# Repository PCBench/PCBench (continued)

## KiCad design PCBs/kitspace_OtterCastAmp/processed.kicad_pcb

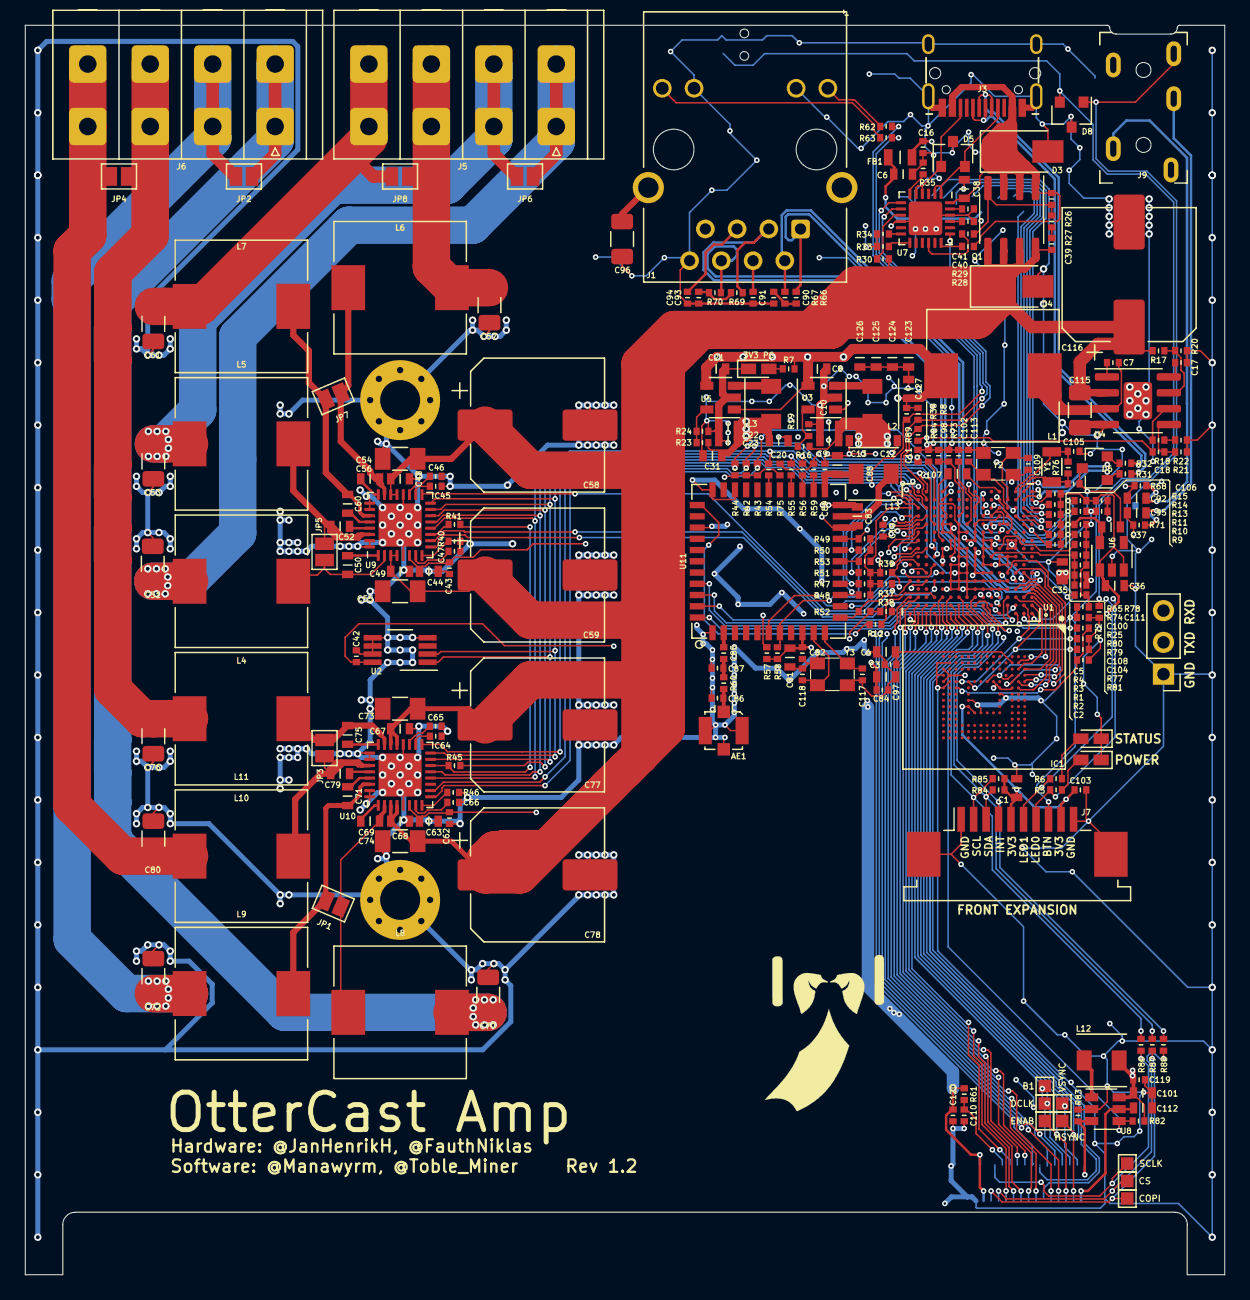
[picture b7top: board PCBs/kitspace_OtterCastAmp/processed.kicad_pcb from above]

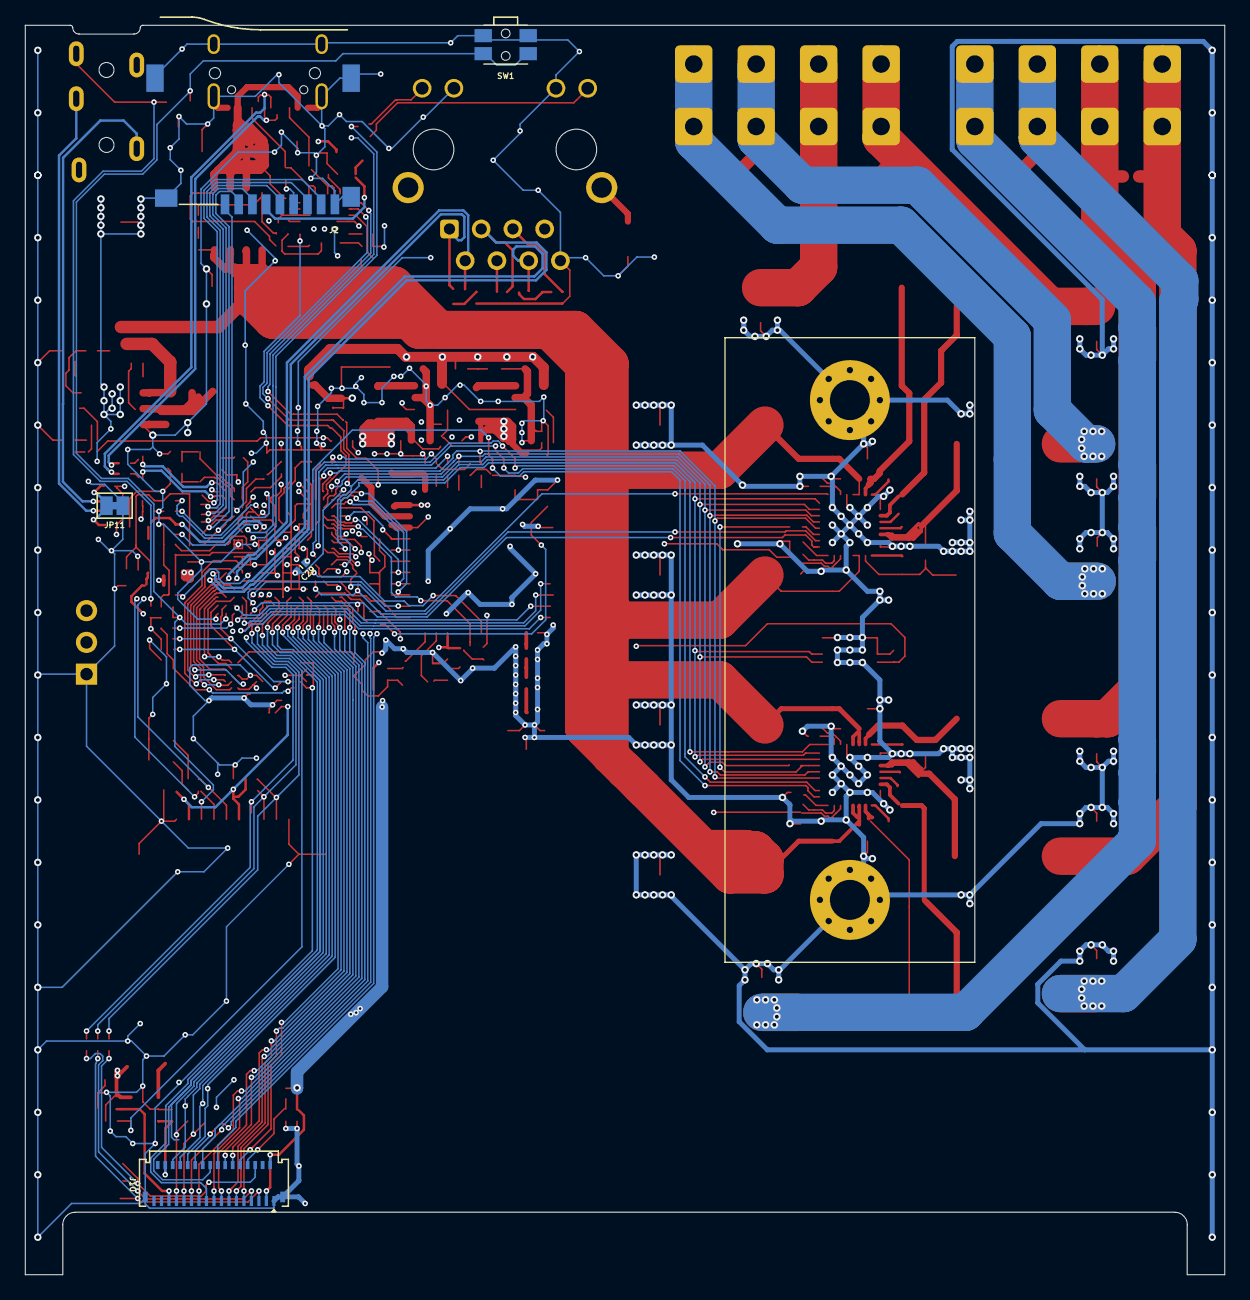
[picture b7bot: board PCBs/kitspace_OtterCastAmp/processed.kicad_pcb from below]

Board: 4 copper layers, 96.0 x 100.0 mm, 269 parts (5 on the bottom side), 203 nets.

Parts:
3V3 PG: LED; LED_0603_1608Metric
AE1: u.FL; U.FL_Molex_MCRF_73412-0110_Vertical
B1: TestPoint; TestPoint_Pad_1.0x1.0mm
C1, C4, C6, C8, C9, C10, C12, C13, C20, C21, C22, C23, C31, C35, C36, C37, C44, C63, C81, C83, C88, C97, C101, C107, C123, C124, C125, C126, C127: 10u; C_0603
C2, C86, C87: DNP; C_0402
C3, C5, C11, C16, C17, C19, C29, C39, C42, C43, C62, C82, C84, C89, C90, C91, C93, C94, C98, C100, C102, C103, C104, C108, C110, C111, C119, C120: 100n; C_0402
C7: 10n; C_0402
C18: 3.3n; C_0402
C38, C92, C95: 1u 25V; C_0603
C40, C41, C45, C46, C47, C64, C65, C66: 1u; C_0402
C48, C49, C67, C68: 100n 50V; C_0603
C50, C52, C56, C60, C69, C71, C75, C79, C112: 470n 25V; C_0603
C51, C53, C57, C61, C70, C72, C76, C80: 680n 50V; C_1206_3216Metric
C54, C55, C73, C74, C115: 22u 50V; C_1206_3216Metric
C58, C59, C77, C78, C116: 470u 35V; CP_Elec_10x10.5
C85, C105, C106, C109, C113: 18p; C_0402
C96: 1n 2kV; C_1206_3216Metric
C117, C118: 22pF; C_0402
COPI: TestPoint; TestPoint_Pad_1.0x1.0mm
CS: TestPoint; TestPoint_Pad_1.0x1.0mm
D1, D2: LED; LED_0603_1608Metric
D3, D4: SMAJ22A; D_SMA
D5, D6, D8: ESD5302F; SOT-23
DCLK: TestPoint; TestPoint_Pad_1.0x1.0mm
ENAB: TestPoint; TestPoint_Pad_1.0x1.0mm
FB1: FERRET; R_0805
H1, H2: 3.2mm; MountingHole_3.2mm_M3_Pad_Via
HSYNC: TestPoint; TestPoint_Pad_1.0x1.0mm
IC1: EMMC04G-S100-B08U; MICRON_EMMC_153
J1: HR911105A; RJ45_Hanrun_HR911105A
J2: Micro_SD_Card; SUNTECH_ST-TF-003A
J3: USB; USB-C 16Pin
J4: UART1; PinHeader_1x03_P2.54mm_Vertical
J5, J6: C475204
J7: AFA07-S10FCC-00; TE_1-84952-0_1x10-1MP_P1.0mm_Horizontal
J9: PJ-3270
J10: FH26W-33S-0.3SHW; Molex_502250-3391_2Rows-33Pins-1MP_P0.60mm_Horizontal
JP1, JP2, JP3, JP4, JP5, JP6, JP7, JP8: PBTL; SolderJumper-2_P1.3mm_Open_Pad1.0x1.5mm
JP11: GNDA; SolderJumper-2_P1.3mm_Bridged_Pad1.0x1.5mm
L1: 15uH; L_10.4x10.4_H4.8
L2, L3: 2u2; Inductor_4040
L4, L5, L6, L7, L8, L9, L10, L11: 10u; L_10.4x10.4_H4.8
L12: 22u; Inductor_4040
L13: 2.2uH; Inductor_4040
Q1: DMP4015SS; SOIC-8_3.9x4.9mm_P1.27mm
R1, R2, R4, R9, R10, R11, R13, R14, R15, R18, R20, R47, R48, R49, R50, R51, R52, R57, R58, R61: 47k; R_0402
R3, R12, R25, R53, R59, R64: 22; R_0402
R5, R6, R7, R8, R28, R36, R62, R63, R77, R79, R84, R85, R89: 2.2k; R_0402
R16, R17, R23, R24, R26, R33, R34, R35, R78: 100k; R_0402
R19: 68k; R_0402
R21: 15k; R_0402
R22, R75: 5.6k; R_0402
R27, R54, R55, R56: 100R; R_0402
R29: 22k; R_0402
R30, R46: 1k; R_0402
R31, R32, R40, R41, R60, R86, R87, R88: 0R; R_0402
R37, R38, R39, R42, R43, R44, R65, R82: 10k; R_0402
R45, R68, R71: DNP; R_0402
R66, R67, R69, R70: 51; R_0402
R72, R73: 200k; R_0402
R74: 6k04; R_0402
R76: 10M; R_0402
R80, R81: 240; R_0402
R83: 10R; R_0402
SCLK: TestPoint; TestPoint_Pad_1.0x1.0mm
SW1: CONFIG; SW_SPST_EVQP7C
U1: AllWinner-S3(FBGA-234); FBGA-234(Pitch-0.65mm_Pad-0.3mm_11x11x1.08mm)
U2: LM75B; VSSOP-8_3.0x3.0mm_P0.65mm
U3, U5: SY8089AAAC; SOT-23-5
U4: MP2303; SOIC-8-1EP_3.9x4.9mm_P1.27mm_EP2.29x3mm
U6: MIC5501-3.0YM5; SOT-23-5
U7: STUSB4500; QFN-24-1EP_4x4mm_P0.5mm_EP2.7x2.7mm
U8: AP3019A; SOT-23-6
U9, U10: TAS5825MRHB; Texas_S-PVQFN-N32_EP3.45x3.45mm
U11: AP6236; LGA_44_12x12mm_0.9mm
VSYNC: TestPoint; TestPoint_Pad_1.0x1.0mm
Y1: 32.768kHz; Crystal_SMD_3215-2Pin_3.2x1.5mm
Y2: 24MHz; Oscillator_3225
Y3: 26MHz; Oscillator_3225

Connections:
+1.1V: C19.1, C20.1, C22.1, C23.1, C29.1, C31.1, L3.2, R23.1, U1.G12, U1.H12, U1.J11, U1.J12, U1.K8, U1.K9, U1.K11, U1.L8, U1.M8, U1.N5
+1V5: C9.1, C10.1, C11.1, C12.1, C13.1, C35.1, C104.2, L2.2, R16.1, R77.2, U1.F6, U1.F7, U1.F8, U1.G8, U1.H8, U1.J8
+3.0VA: C37.1, C100.1, U1.L6, U1.M7, U6.5
+3V3: C1.1, C8.1, C16.1, C21.1, C36.1, C42.1, C43.2, C44.2, C62.2, C63.2, C81.1, C82.1, C83.1, C84.1, C97.1, C101.1, C103.1, C119.1, C120.1, C123.1, C124.1, C125.1, C126.1, C127.1, FB1.1, IC1.C6, IC1.E6, IC1.F5, IC1.J10, IC1.K9, IC1.M4, IC1.N4, IC1.P3, IC1.P5, J7.5, J7.9, J10.2, J10.3, L1.2, L12.1, R1.1, R2.1, R4.1, R7.1, R8.1, R9.2, R10.2, R11.2, R13.2, R14.2, R15.2, R18.1, R36.1, R37.1, R38.1, R39.1, R42.1, R43.1, R44.1, R47.1, R48.1, R49.1, R50.1, R51.1, R52.1, R57.1, R58.1, R61.1, R65.2, R72.1, R75.2, R78.1, R82.1, R84.1, R85.1, R89.1, U1.H11, U1.L11, U1.L12, U1.M4, U1.M5, U1.M11, U1.M12, U1.N6, U1.N7, U1.P5, U1.P12, U2.8, U3.1, U3.4, U5.1, U5.4, U6.1, U6.3, U8.6, U9.6, U10.6, U11.9, U11.22
AMP_FAULT0: R38.2, U1.A5, U9.9
AMP_FAULT1: R43.2, U1.B5, U10.9
AMP_MUTE0: R37.2, U1.E13, U9.10
AMP_MUTE1: R42.2, U1.J13, U10.10
AMP_PDN0: R39.2, U1.G15, U9.17
AMP_PDN1: R44.2, U1.H13, U10.17
AP-CK32KO: R59.1, R75.1, U1.P3
AP-WAKE-BT: U1.F12, U11.6
B1: B1.1, J10.24, U1.C11
B2: J10.23, U1.J14
B3: J10.22, U1.J15
B4: J10.21, U1.B16
B5: J10.20, U1.C16
BT-DIS-N: R12.2, U11.34
BT-UART-CTS: U1.B8, U11.44
BT-UART-RTS: U1.C4, U11.41
BT-UART-RX: R57.2, U1.B3, U11.43
BT-UART-TX: U1.B4, U11.42
BT-WAKE-AP: R58.2, U1.N14, U11.7
EPHY_LINK_LED: R62.1, U1.K5
EPHY_RX_N: J1.6, R70.1, U1.F1
EPHY_RX_P: J1.3, R69.1, U1.F2
EPHY_SPD_LED: R63.1, U1.L5
EPHY_TX_N: J1.2, R67.1, U1.E2
EPHY_TX_P: J1.1, R66.1, U1.E3
G0: J10.19, U1.B9
G1: J10.18, U1.A9
G2: J10.17, U1.C15
G3: J10.16, U1.L15
G4: J10.15, U1.A15
G5: J10.14, U1.B15
GND: 3V3 PG.1, AE1.2, C1.2, C2.2, C3.2, C4.2, C5.2, C6.2, C8.2, C9.2, C10.2, C11.2, C12.2, C13.2, C16.2, C17.2, C19.2, C20.2, C21.2, C22.2, C23.2, C29.2, C31.2, C35.2, C36.2, C37.2, C38.1, C40.1, C41.1, C42.2, C43.1, C44.1, C45.1, C46.1, C47.1, C48.2, C49.2, C51.1, C53.2, C54.2, C55.2, C57.1, C58.2, C59.2, C61.2, C62.1, C63.1, C64.1, C65.1, C66.1, C67.2, C68.2, C70.1, C72.2, C73.2, C74.2, C76.1, C77.2, C78.2, C80.2, C81.2, C82.2, C83.2, C84.2, C86.1, C87.1, C88.2, C89.2, C90.1, C91.1, C93.1, C94.1, C96.2, C97.2, C98.2, C100.2, C101.2, C102.2, C103.2, C105.2, C106.2, C107.2, C108.2, C109.2, C110.2, C111.2, C112.1, C113.2, C115.2, C116.2, C117.2, C118.2, C119.2, C120.2, C123.2, C124.2, C125.2, C126.2, C127.2, D1.1, D2.1, D3.2, D4.2, D5.3, D6.3, D8.3, H1.1, H2.1, IC1.C4, IC1.E7, IC1.G5, IC1.H10, IC1.K8, IC1.N2, IC1.N5, IC1.P4, IC1.P6, J1.8, J1.10, J1.11, J2.6, J2.9, J3.A1, J3.A12, J3.B1, J3.B12, J3.S1, J4.1, J7.1, J7.10, J7.MP, J10.1, J10.MP, JP11.1, R19.2, R20.1, R21.2, R22.2, R24.2, R25.2, R33.1, R34.1, R35.2, R40.2, R46.2, R64.2, R73.2, R74.1, R79.2, R80.2, R81.2, R83.2, SW1.2, U1.A1, U1.A16, U1.C9, U1.D4, U1.D5, U1.D6, U1.D7, U1.D8, U1.D9, U1.D10, U1.D11, U1.D12, U1.E4, U1.E5, U1.E6, U1.E7, U1.E8, U1.E9, U1.E10, U1.E11, U1.E14, U1.F9, U1.F10, U1.F11, U1.G4, U1.G5, U1.G6, U1.G7, U1.G9, U1.G10, U1.G11, U1.H3, U1.H4, U1.H5, U1.H7, U1.H9, U1.H10, U1.J3, U1.J4, U1.J6, U1.J7, U1.J9, U1.J10, U1.K3, U1.K4, U1.K6, U1.K7, U1.K10, U1.K12, U1.L4, U1.L7, U1.L9, U1.L10, U1.M10, U1.N4, U1.N8, U1.P8, U1.R5, U1.T1, U1.T16, U2.4, U2.5, U2.6, U2.7, U3.2, U4.4, U4.9, U5.2, U6.2, U7.10, U7.22, U7.25, U8.2, U9.5, U9.20, U9.25, U9.26, U9.31, U9.32, U9.33, U10.5, U10.20, U10.25, U10.26, U10.31, U10.32, U10.33, U11.1, U11.20, U11.31, U11.33, U11.36, Y2.2, Y2.4, Y3.2, Y3.4
GNDA: J9.3, JP11.2, R68.1, R71.1
GPIO_BTN: C5.1, D8.2, J7.8, R4.2, SW1.1, U1.A2
GPIO_LED0: J7.7, R5.1, U1.F14
GPIO_LED1: J7.6, R6.1, U1.G13
I2C0_INT: J7.4, R88.2, U1.C6
I2C0_SCL: J7.2, R85.2, R86.2, U1.A7
I2C0_SDA: J7.3, R84.2, R87.2, U1.B7
I2C1_INT: R89.2, U1.R14, U7.19
I2C1_SCL: R36.2, U1.G16, U2.2, U7.7, U9.16, U10.16
I2C1_SDA: R8.2, U1.J16, U2.1, U7.8, U9.15, U10.15
LCD_CS: CS.1, J10.7, R88.1
LCD_DCLK: DCLK.1, J10.26, U1.A11
LCD_ENAB: ENAB.1, J10.25, U1.B11
LCD_HSYNC: HSYNC.1, J10.27, U1.C10
LCD_PWM: R82.2, U1.C8, U8.4
LCD_RESET: C110.1, J10.8, R61.2
LCD_SCL: J10.6, R86.1, SCLK.1
LCD_SDA: COPI.1, J10.5, R87.1
LCD_VSYNC: J10.28, U1.B10, VSYNC.1
LEDA: C112.2, J10.29, U8.5
LEDK: J10.30, R83.1, U8.3
LINE_DET: D8.1, J9.4, R72.2, U1.C7
LINE_L: C92.1, R68.2, U1.R12
LINE_R: C95.2, R71.2, U1.T12
unnamed: AE1.1, C86.2, R60.2
unnamed: C3.1, C4.1, IC1.C2
unnamed: C6.1, FB1.2, J2.4
unnamed: C7.1, L1.1, U4.3
unnamed: C7.2, U4.1
unnamed: C17.1, U4.8
unnamed: C18.1, R22.1
unnamed: C18.2, U4.6
unnamed: C38.2, D3.1, J3.A4, J3.A9, J3.B4, J3.B9, Q1.1, Q1.2, Q1.3, R26.2, R28.2, U7.24
unnamed: C39.2, R27.1
unnamed: C40.2, U7.21
unnamed: C41.2, U7.23
unnamed: C45.2, U9.18
unnamed: C46.2, U9.19
unnamed: C47.2, U9.7
unnamed: C50.1, JP5.1, L4.1, U9.2
unnamed: C50.2, U9.1
unnamed: C51.2, J5.1, JP6.1, L4.2
unnamed: C52.1, JP5.2, L5.2, U9.30
unnamed: C52.2, U9.29
unnamed: C53.1, J5.2, JP6.2, L5.1
unnamed: C56.1, JP7.1, L6.1, U9.23
unnamed: C56.2, U9.24
unnamed: C57.2, J5.3, JP8.1, L6.2
unnamed: C60.1, JP7.2, L7.2, U9.27
unnamed: C60.2, U9.28
unnamed: C61.1, J5.4, JP8.2, L7.1
unnamed: C64.2, U10.18
unnamed: C65.2, U10.19
unnamed: C66.2, U10.7
unnamed: C69.1, JP1.1, L8.1, U10.2
unnamed: C69.2, U10.1
unnamed: C70.2, J6.1, JP2.1, L8.2
unnamed: C71.1, JP1.2, L9.2, U10.30
unnamed: C71.2, U10.29
unnamed: C72.1, J6.2, JP2.2, L9.1
unnamed: C75.1, JP3.1, L10.1, U10.23
unnamed: C75.2, U10.24
unnamed: C76.2, J6.3, JP4.1, L10.2
unnamed: C79.1, JP3.2, L11.2, U10.27
unnamed: C79.2, U10.28
unnamed: C80.1, J6.4, JP4.2, L11.1
unnamed: C85.1, C87.2, R60.1
unnamed: C85.2, U11.2
unnamed: C88.1, C89.1, L13.1, U11.23
unnamed: C90.2, R66.2, R67.2
unnamed: C91.2, J1.4
unnamed: C92.2, J9.2
unnamed: C93.2, R69.2, R70.2
unnamed: C94.2, J1.5
unnamed: C95.1, J9.5
unnamed: C96.1, J1.SH
unnamed: C98.1, R73.1, U1.N10
unnamed: C102.1, U1.M9
unnamed: C104.1, C108.1, R77.1, R79.1, U1.H6
unnamed: C105.1, R76.2, U1.T3, Y1.1
unnamed: C106.1, R76.1, U1.R3, Y1.2
unnamed: C107.1, U1.T5
unnamed: C109.1, U1.R4, Y2.1
unnamed: C113.1, U1.P4, Y2.3
unnamed: C117.1, U11.11, Y3.3
unnamed: C118.1, U11.10, Y3.1
unnamed: D1.2, R5.2
unnamed: D2.2, R6.2
unnamed: D5.1, J3.B5, U7.4, U7.5
unnamed: D5.2, J3.A5, U7.1, U7.2
unnamed: 3V3 PG.2, R7.2
unnamed: J1.9, R62.2
unnamed: J1.12, R63.2
unnamed: J3.A6, J3.B6, R32.1
unnamed: J3.A7, J3.B7, R31.1
unnamed: L2.1, U3.3
unnamed: L3.1, U5.3
unnamed: L12.2, U8.1
unnamed: L13.2, U11.21
unnamed: Q1.4, R26.1, R27.2, R29.2
unnamed: R3.2, U1.A3
unnamed: R12.1, U1.C13
unnamed: R16.2, R19.1, U3.5
unnamed: R17.1, R20.2, U4.7
unnamed: R18.2, R21.1, U4.5
unnamed: R23.2, R24.1, U5.5
unnamed: R25.1, U1.M6
unnamed: R28.1, U7.18
unnamed: R29.1, U7.16
unnamed: R30.1, U7.9
unnamed: R33.2, U7.13
unnamed: R34.2, U7.12
unnamed: R35.1, U7.6
unnamed: R40.1, U9.8
unnamed: R41.1, R45.1, U10.14
unnamed: R41.2, U9.11
unnamed: R46.1, U10.8
unnamed: R53.2, U11.17
unnamed: R54.2, U11.28
unnamed: R55.2, U11.26
unnamed: R56.2, U11.25
unnamed: R59.2, U11.24
unnamed: R64.1, U1.R13
unnamed: R65.1, U1.R7
unnamed: R74.2, U1.P6
unnamed: R80.1, U1.J5
unnamed: R81.1, U1.F5
PCM_BCLK: R55.1, U1.P14, U9.13, U10.13
PCM_DIN: R56.1, U1.M13
PCM_DOUT: R45.2, U1.T15, U9.14
PCM_LRCLK: R54.1, U1.T14, U9.12, U10.12
R1: J10.13, U1.A14
R2: J10.12, U1.B13
R3: J10.11, U1.A13
R4: J10.10, U1.B12
R5: J10.9, U1.C12
RESETn: C111.1, R78.2, U1.P7
SDC0_CLK: J2.5, R13.1, U1.P2
SDC0_CMD: J2.3, R11.1, U1.N2
SDC0_D0: J2.7, R14.1, U1.P1
SDC0_D1: J2.8, R15.1, U1.R1
SDC0_D2: J2.1, R9.1, U1.M2
SDC0_D3: J2.2, R10.1, U1.N3
SDC2_CLK: C2.1, IC1.M6, R3.1
SDC2_CMD: IC1.M5, R1.2, U1.B2
SDC2_D0: IC1.A3, U1.C2
SDC2_D1: IC1.A4, U1.F3
SDC2_D2: IC1.A5, U1.F4
SDC2_D3: IC1.B2, U1.C1
SDC2_D4: IC1.B3, U1.C3
SDC2_D5: IC1.B4, U1.D3
SDC2_D6: IC1.B5, U1.D2
SDC2_D7: IC1.B6, U1.D1
SDC2_RST: IC1.K5, R2.2, U1.B1
UART1_RX: J4.3, U1.M14
UART1_TX: J4.2, U1.M15
USB-D_N: D6.1, R31.2, U1.R2
USB-D_P: D6.2, R32.2, U1.T2
VBUS: C39.1, C48.1, C49.1, C54.1, C55.1, C58.1, C59.1, C67.1, C68.1, C73.1, C74.1, C77.1, C78.1, C115.1, C116.1, D4.1, Q1.5, Q1.6, Q1.7, Q1.8, R17.2, R30.2, U4.2, U9.3, U9.4, U9.21, U9.22, U10.3, U10.4, U10.21, U10.22
WL-PMU-EN: R52.2, U1.E16, U11.12
WL-SDIO-CLK: R53.1, U1.P16
WL-SDIO-CMD: R51.2, U1.N15, U11.16
WL-SDIO-D0: R50.2, U1.P15, U11.18
WL-SDIO-D1: R49.2, U1.N16, U11.19
WL-SDIO-D2: R48.2, U1.R15, U11.14
WL-SDIO-D3: R47.2, U1.R16, U11.15
WL-WAKE-AP: U1.C5, U11.13
